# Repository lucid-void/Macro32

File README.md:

# Macro32

The Macro32 is a macropad featuring a stm32.
This project was a way for me to learn how to integrate an IC of my choosing on my PCB.
It was also my fist project using kicad

## Take a look

[kicad project](https://kicanvas.org/?github=https://github.com/KillrOfLife/Macro32/blob/main/PCB/macro32.kicad_pro)

## How can I make it myself

Great question!
Go look in the github releases for the latest tag
There you should find the downloads for the PCB production files (aka gerbers)
And the STL's for the case parts if you want that too. (you may need to download the source code)

## How to assemble

For any help assembling this macropad refer to the [build guide](https://github.com/KillrOfLife/Macro32/blob/main/buildguide.md).

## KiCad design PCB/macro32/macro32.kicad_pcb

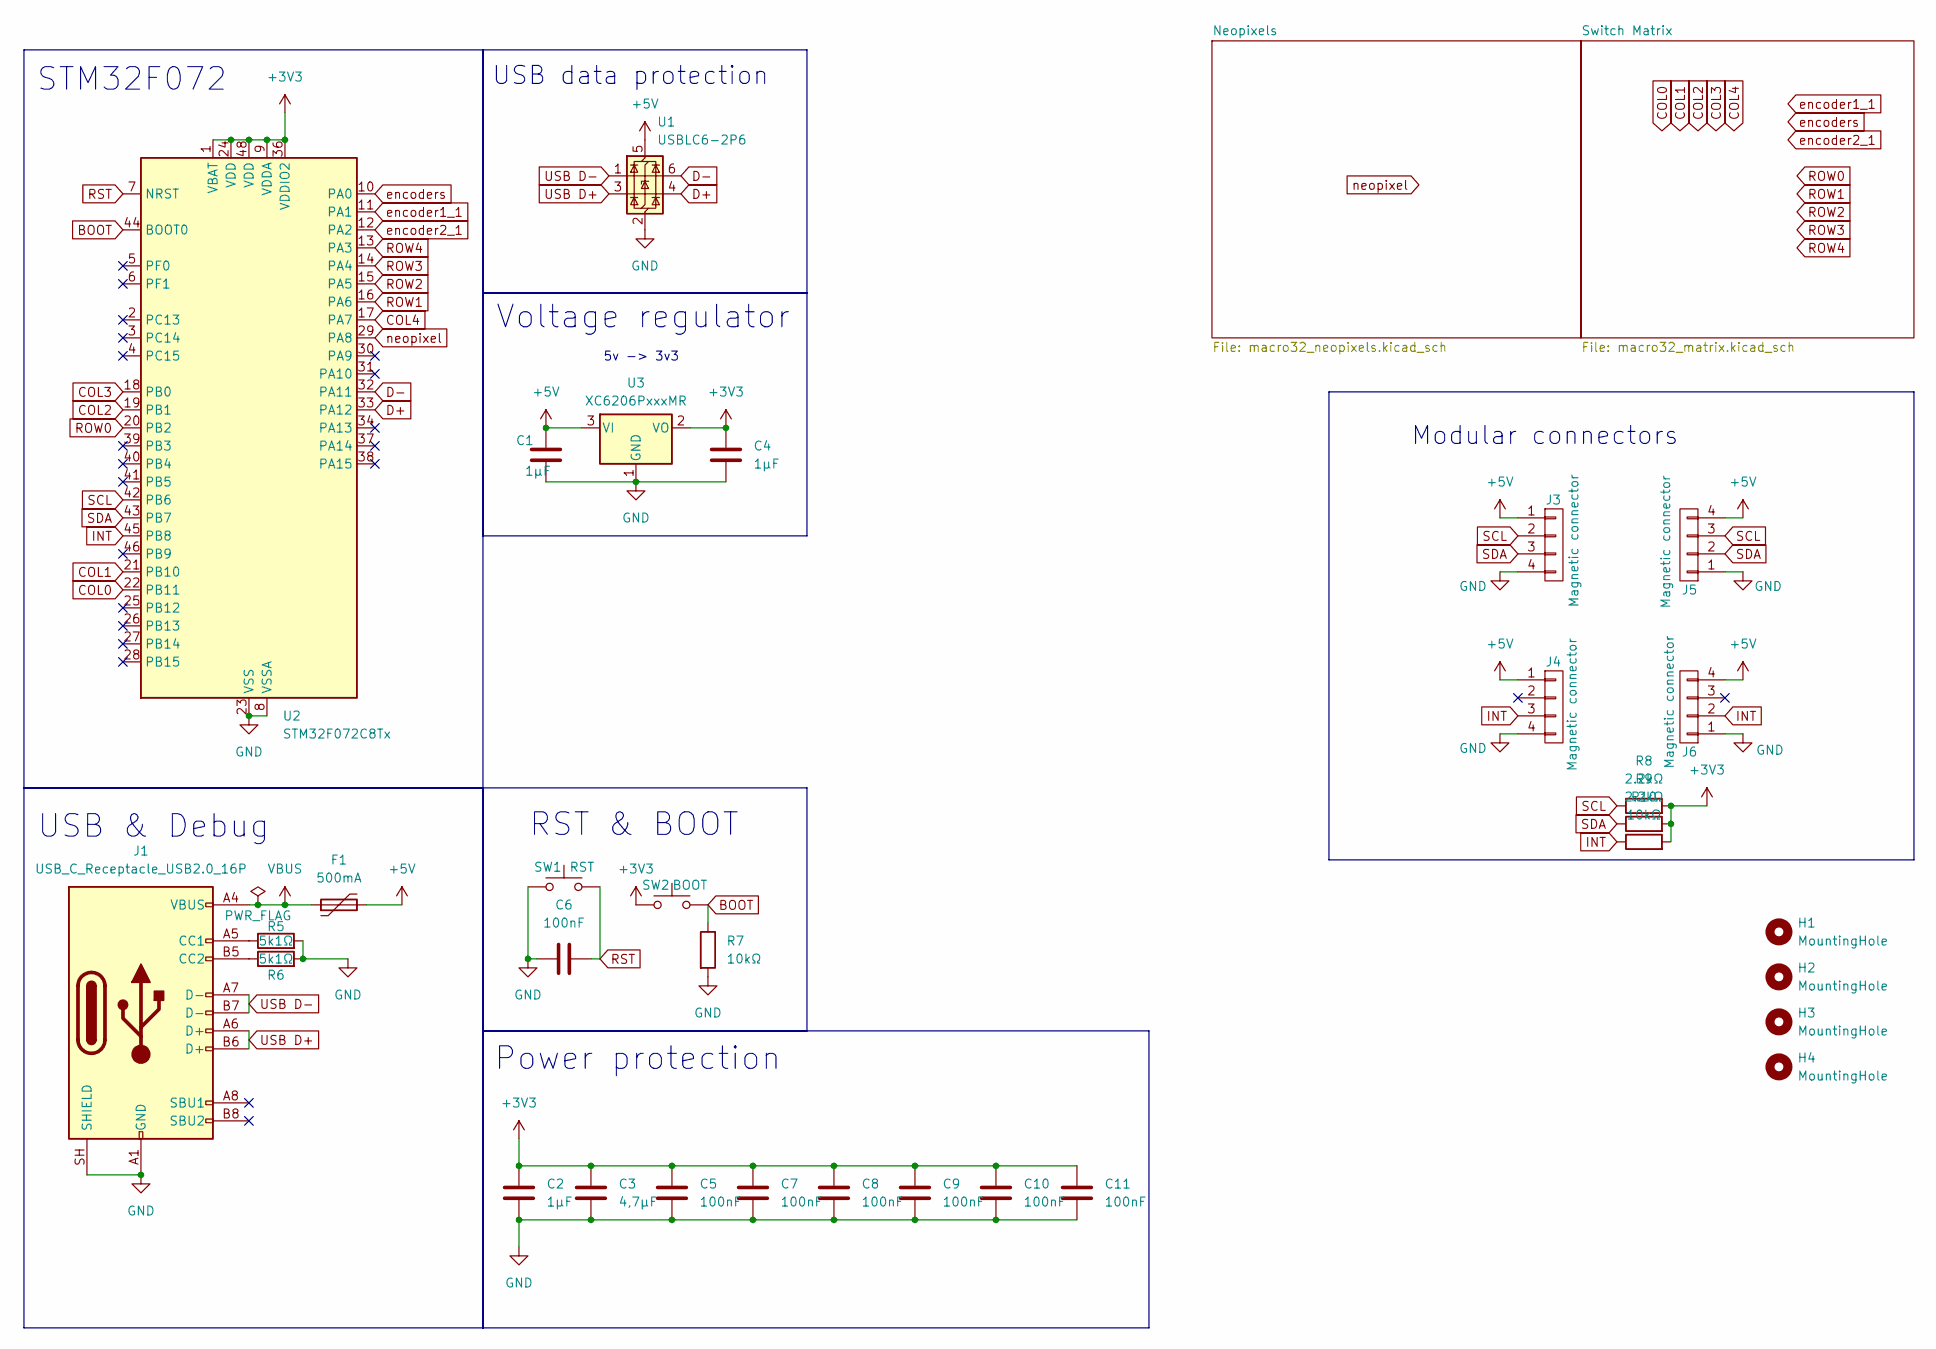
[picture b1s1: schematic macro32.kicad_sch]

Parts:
C1, C2, C4: 1μF; C_0805_2012Metric_Pad1.18x1.45mm_HandSolder
C3: 4,7μF; C_0805_2012Metric_Pad1.18x1.45mm_HandSolder
C5, C6, C7, C8, C9, C10, C11: 100nF; C_0805_2012Metric_Pad1.18x1.45mm_HandSolder
F1: 500mA; Resistor_1206
H1, H2, H3, H4: MountingHole; MountingHole_3.2mm_M3
J1: USB_C_Receptacle_USB2.0_16P; USB_C_Receptacle_GCT_USB4110
J3, J4, J5, J6: Magnetic connector; fakemag4pin90degFemale
R5, R6: 5k1Ω; Resistor_0805
R7, R10: 10kΩ; Resistor_0805
R8, R9: 2.2kΩ; Resistor_0805
SW1: RST; SW_SPST_TS-1088-xR020
SW2: BOOT; SW_SPST_TS-1088-xR020
U1: USBLC6-2P6; SOT-666
U2: STM32F072C8Tx; LQFP-48_7x7mm_P0.5mm
U3: XC6206PxxxMR; SOT-23-3

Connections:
+3V3: C2.1, C3.1, C4.1, C5.1, C7.1, C8.1, C9.1, C10.1, C11.1, R8.2, R9.2, R10.2, SW2.1, U2.1 (VBAT), U2.9 (VDDA), U2.24 (VDD), U2.36 (VDDIO2), U2.48 (VDD), U3.2 (VO)
+5V: C1.1, F1.2, J3.1, J4.1, J5.4, J6.4, U1.5 (VBUS), U3.3 (VI); also elsewhere on the board
BOOT: R7.1, SW2.2, U2.44 (BOOT0)
COL0: U2.22 (PB11); also elsewhere on the board
COL1: U2.21 (PB10); also elsewhere on the board
COL2: U2.19 (PB1); also elsewhere on the board
COL3: U2.18 (PB0); also elsewhere on the board
COL4: U2.17 (PA7); also elsewhere on the board
D+: U1.4 (I/O2), U2.33 (PA12)
D-: U1.6 (I/O1), U2.32 (PA11)
GND: C1.2, C2.2, C3.2, C4.2, C5.2, C6.1, C7.2, C8.2, C9.2, C10.2, C11.2, J1.A1 (GND), J1.A12 (GND), J1.B1 (GND), J1.B12 (GND), J1.SH (SHIELD), J3.4, J4.4, J5.1, J6.1, R5.2, R6.2, R7.2, SW1.1, U1.2 (GND), U2.8 (VSSA), U2.23 (VSS), U2.35 (VSS), U2.47 (VSS), U3.1 (GND); also elsewhere on the board
INT: J4.3, J6.2, R10.1, U2.45 (PB8)
unnamed: J1.A5 (CC1), R5.1
unnamed: J1.B5 (CC2), R6.1
ROW0: U2.20 (PB2); also elsewhere on the board
ROW1: U2.16 (PA6); also elsewhere on the board
ROW2: U2.15 (PA5); also elsewhere on the board
ROW3: U2.14 (PA4); also elsewhere on the board
ROW4: U2.13 (PA3); also elsewhere on the board
RST: C6.2, SW1.2, U2.7 (NRST)
SCL: J3.2, J5.3, R8.1, U2.42 (PB6)
SDA: J3.3, J5.2, R9.1, U2.43 (PB7)
USB D+: J1.A6 (D+), J1.B6 (D+), U1.3 (I/O2)
USB D-: J1.A7 (D-), J1.B7 (D-), U1.1 (I/O1)
VBUS: F1.1, J1.A4 (VBUS), J1.A9 (VBUS), J1.B4 (VBUS), J1.B9 (VBUS)
encoder1_1: U2.11 (PA1); also elsewhere on the board
encoder2_1: U2.12 (PA2); also elsewhere on the board
encoders: U2.10 (PA0); also elsewhere on the board
neopixel: U2.29 (PA8); also elsewhere on the board

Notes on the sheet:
STM32F072
RST & BOOT
USB data protection
Modular connectors
5v -> 3v3
USB & Debug
Voltage regulator
Power protection

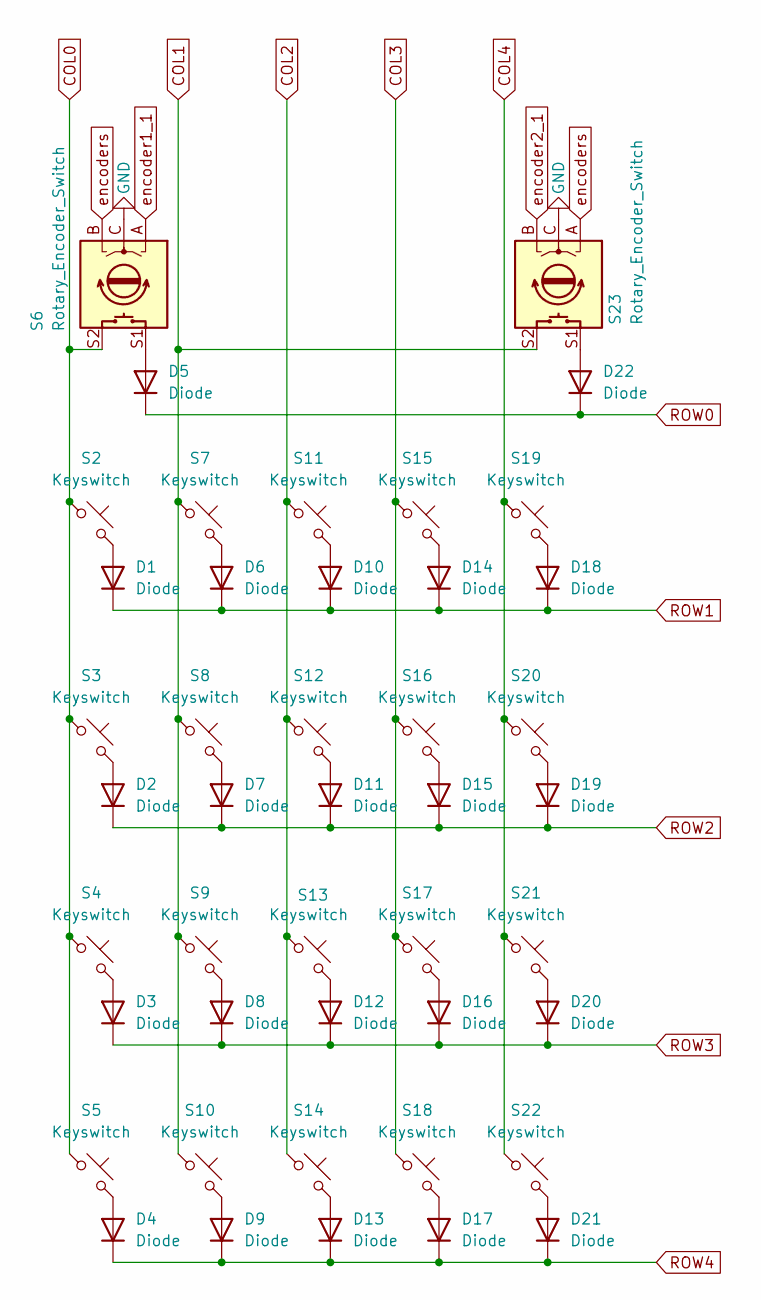
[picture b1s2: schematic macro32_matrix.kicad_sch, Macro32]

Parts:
D1, D2, D3, D4, D5, D6, D7, D8, D9, D10, D11, D12, D13, D14, D15, D16, D17, D18, D19, D20, D21, D22: Diode; Diode_combo
S2, S3, S4, S5, S7, S8, S9, S10, S11, S12, S13, S14, S15, S16, S17, S18, S19, S20, S21, S22: Keyswitch; Hotswap_MX_Plated_1.00u
S6, S23: Rotary_Encoder_Switch; keyswitch_cherrymx_hotswap_1u_rotary_encoder_ec12_1

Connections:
COL0: S2.1, S3.1, S4.1, S5.1, S6.S2; also elsewhere on the board
COL1: S7.1, S8.1, S9.1, S10.1, S23.S2; also elsewhere on the board
COL2: S11.1, S12.1, S13.1, S14.1; also elsewhere on the board
COL3: S15.1, S16.1, S17.1, S18.1; also elsewhere on the board
COL4: S19.1, S20.1, S21.1, S22.1; also elsewhere on the board
GND: S6.C, S23.C; also elsewhere on the board
unnamed: D1.2 (A), S2.2
unnamed: D2.2 (A), S3.2
unnamed: D3.2 (A), S4.2
unnamed: D4.2 (A), S5.2
unnamed: D5.2 (A), S6.S1
unnamed: D6.2 (A), S7.2
unnamed: D7.2 (A), S8.2
unnamed: D8.2 (A), S9.2
unnamed: D9.2 (A), S10.2
unnamed: D10.2 (A), S11.2
unnamed: D11.2 (A), S12.2
unnamed: D12.2 (A), S13.2
unnamed: D13.2 (A), S14.2
unnamed: D14.2 (A), S15.2
unnamed: D15.2 (A), S16.2
unnamed: D16.2 (A), S17.2
unnamed: D17.2 (A), S18.2
unnamed: D18.2 (A), S19.2
unnamed: D19.2 (A), S20.2
unnamed: D20.2 (A), S21.2
unnamed: D21.2 (A), S22.2
unnamed: D22.2 (A), S23.S1
ROW0: D5.1 (K), D22.1 (K); also elsewhere on the board
ROW1: D1.1 (K), D6.1 (K), D10.1 (K), D14.1 (K), D18.1 (K); also elsewhere on the board
ROW2: D2.1 (K), D7.1 (K), D11.1 (K), D15.1 (K), D19.1 (K); also elsewhere on the board
ROW3: D3.1 (K), D8.1 (K), D12.1 (K), D16.1 (K), D20.1 (K); also elsewhere on the board
ROW4: D4.1 (K), D9.1 (K), D13.1 (K), D17.1 (K), D21.1 (K); also elsewhere on the board
encoder1_1: S6.A; also elsewhere on the board
encoder2_1: S23.B; also elsewhere on the board
encoders: S6.B, S23.A; also elsewhere on the board

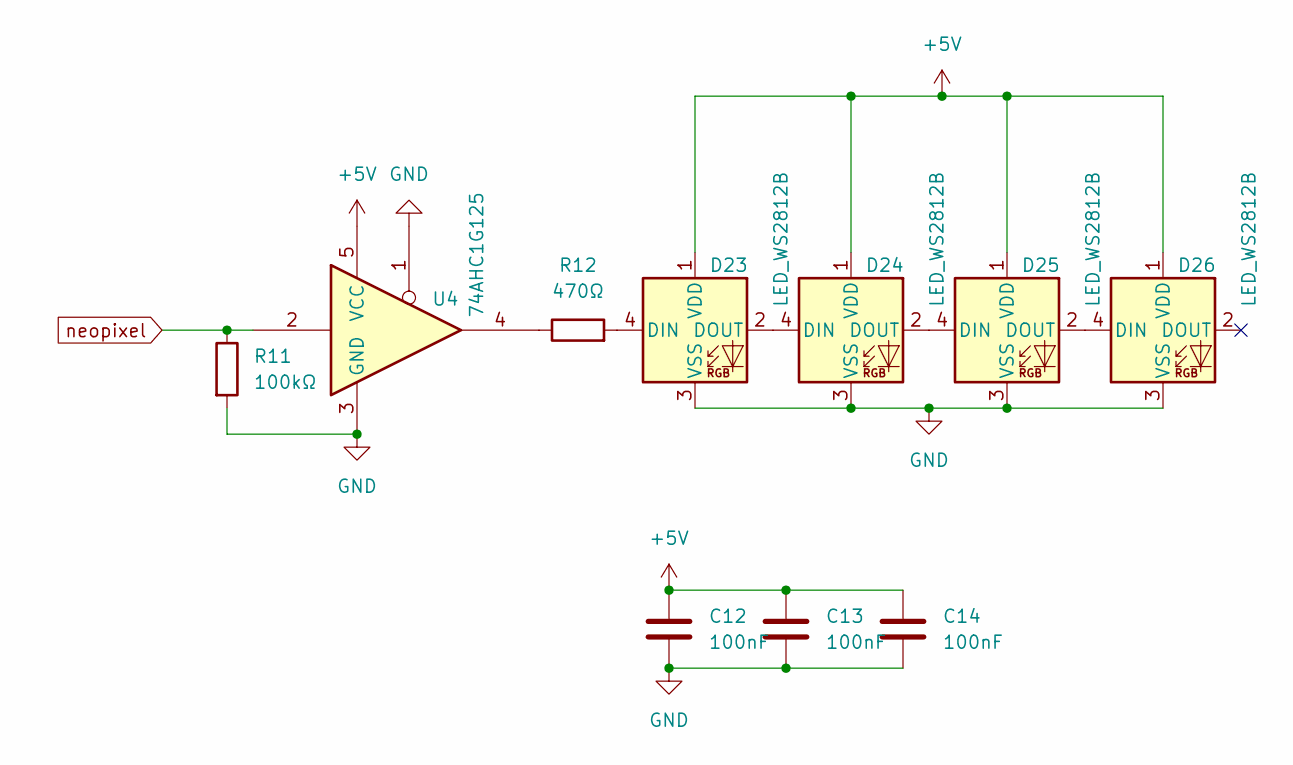
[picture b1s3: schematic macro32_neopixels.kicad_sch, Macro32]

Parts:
C12, C13, C14: 100nF; C_0805_2012Metric_Pad1.18x1.45mm_HandSolder
D23, D24, D25, D26: LED_WS2812B
R11: 100kΩ; Resistor_0805
R12: 470Ω; Resistor_0805
U4: 74AHC1G125; SOT-353_SC-70-5

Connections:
+5V: C12.1, C13.1, C14.1, D23.1 (VDD), D24.1 (VDD), D25.1 (VDD), D26.1 (VDD), U4.5 (VCC); also elsewhere on the board
GND: C12.2, C13.2, C14.2, D23.3 (VSS), D24.3 (VSS), D25.3 (VSS), D26.3 (VSS), R11.2, U4.1, U4.3 (GND); also elsewhere on the board
unnamed: D23.4 (DIN), R12.2
unnamed: D23.2 (DOUT), D24.4 (DIN)
unnamed: D24.2 (DOUT), D25.4 (DIN)
unnamed: D25.2 (DOUT), D26.4 (DIN)
unnamed: R12.1, U4.4
neopixel: R11.1, U4.2; also elsewhere on the board

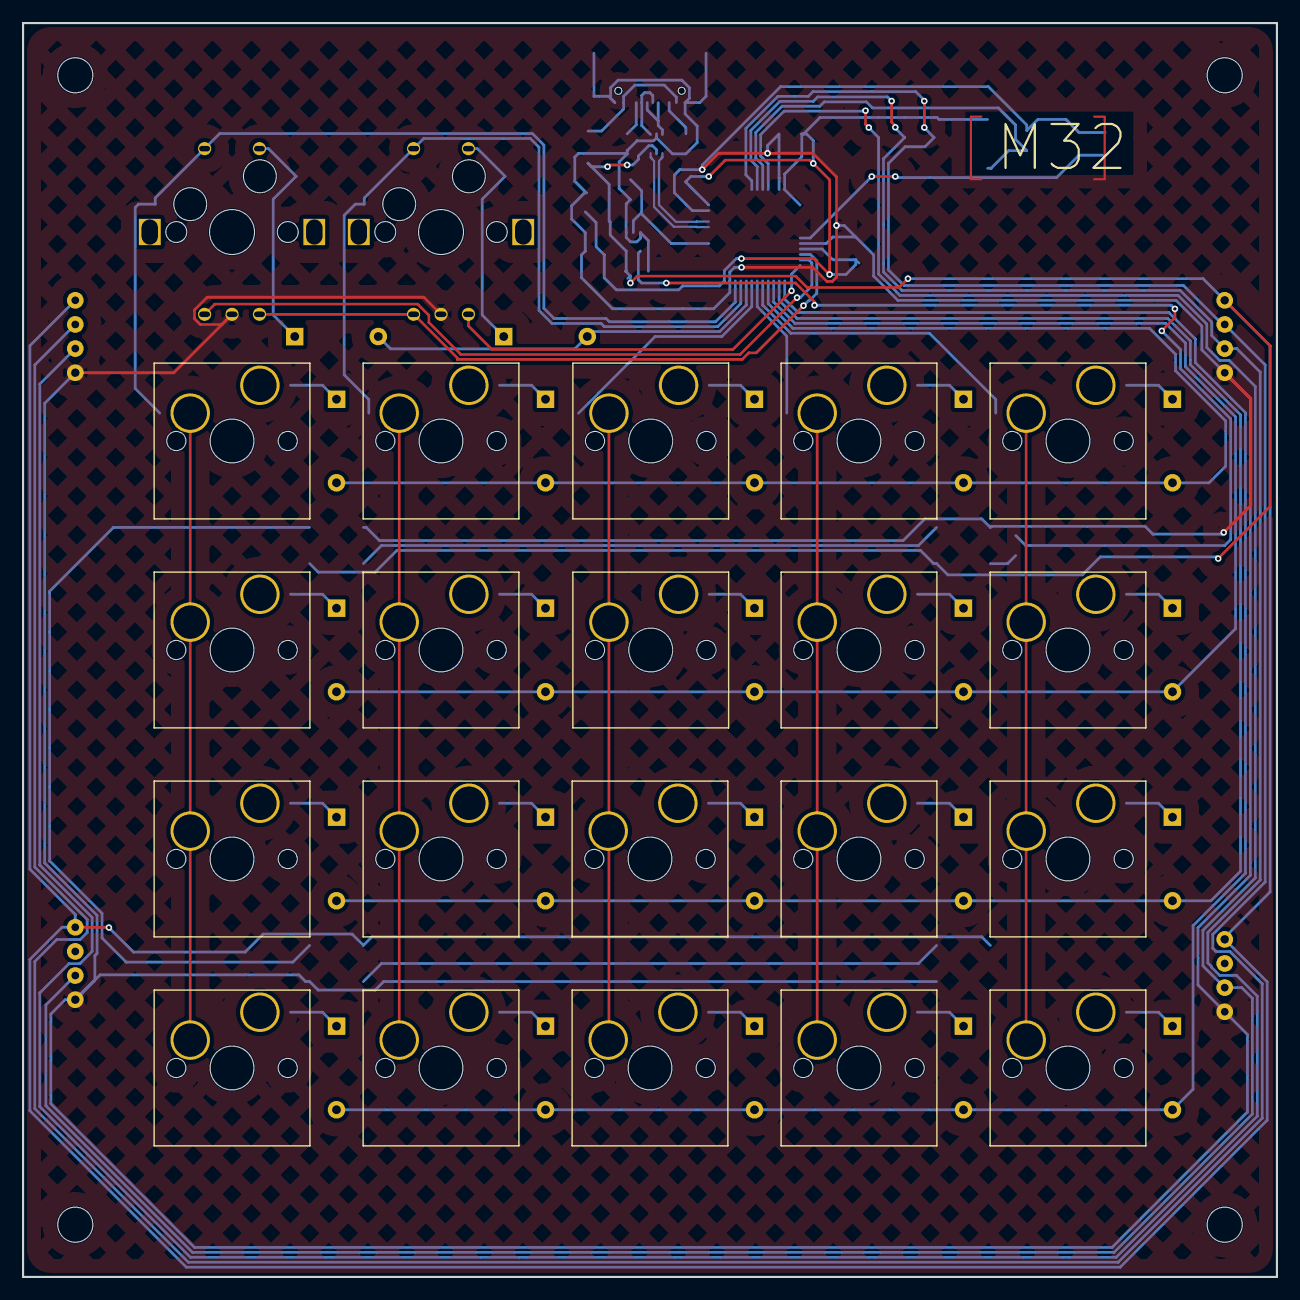
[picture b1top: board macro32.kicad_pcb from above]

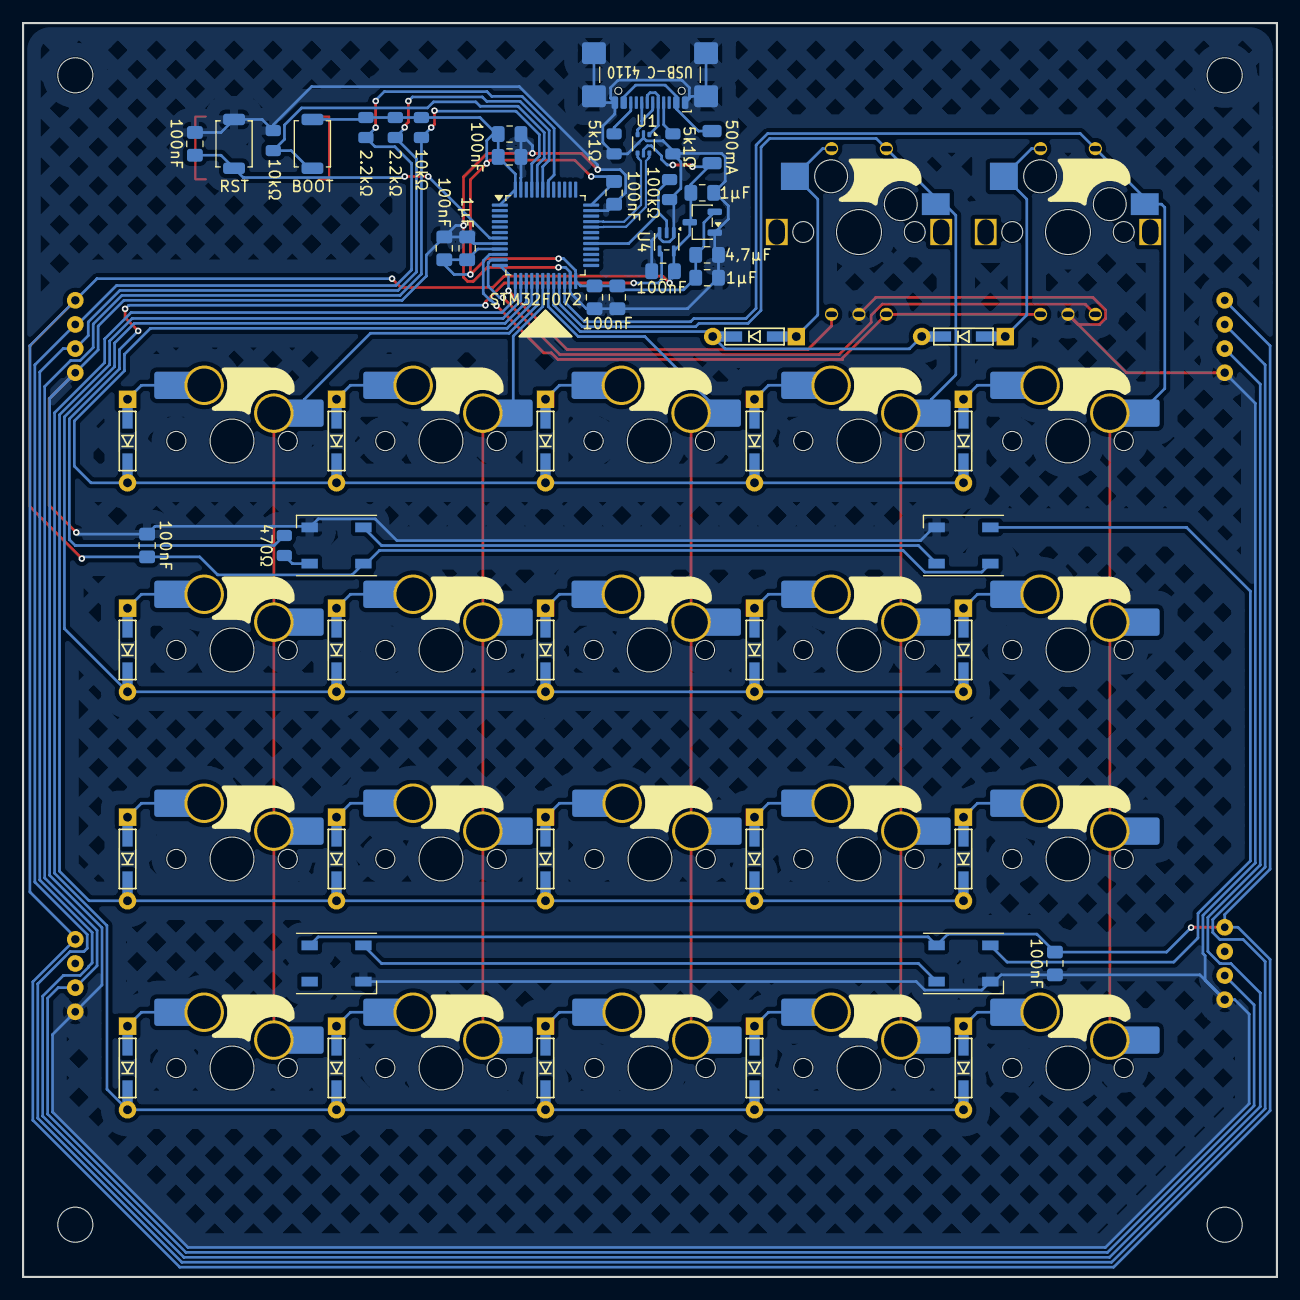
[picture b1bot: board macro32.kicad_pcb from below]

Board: 2 copper layers, 114.3 x 114.3 mm, 86 parts (62 on the bottom side), 56 nets.

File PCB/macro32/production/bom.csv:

Designator,Footprint,Quantity,Value,LCSC Part #
"C1, C2, C4",0805,3,1μF,
"C10, C11, C12, C13, C14, C5, C6, C7, C8, C9",0805,10,100nF,
C3,0805,1,"4,7μF",
"D1, D10, D11, D12, D13, D14, D15, D16, D17, D18, D19, D2, D20, D21, D22, D3, D4, D5, D6, D7, D8, D9",Diode_combo,22,Diode,
"D23, D24, D25, D26",LED_WS2812B,4,LED_WS2812B,
F1,Resistor_1206,1,500mA,
J1,USB_C_Receptacle_GCT_USB4110,1,USB_C_Receptacle_USB2.0_16P,
"J3, J4, J5, J6",fakemag4pin90degFemale,4,Magnetic connector,
"R10, R7",Resistor_0805,2,10kΩ,
R11,Resistor_0805,1,100kΩ,
R12,Resistor_0805,1,470Ω,
"R5, R6",Resistor_0805,2,5k1Ω,
"R8, R9",Resistor_0805,2,2.2kΩ,
"S10, S11, S12, S13, S14, S15, S16, S17, S18, S19, S2, S20, S21, S22, S3, S4, S5, S7, S8, S9",Hotswap_MX_Plated_1.00u,20,Keyswitch,
"S23, S6",keyswitch_cherrymx_hotswap_1u_rotary_encoder_ec12_1,2,Rotary_Encoder_Switch,
SW1,SW_SPST_TS-1088-xR020,1,RST,
SW2,SW_SPST_TS-1088-xR020,1,BOOT,
U1,SOT-666,1,USBLC6-2P6,
U2,LQFP-48_7x7mm_P0.5mm,1,STM32F072,
U3,SOT-23-3,1,XC6206PxxxMR,
U4,SOT-353_SC-70-5,1,74AHC1G125,

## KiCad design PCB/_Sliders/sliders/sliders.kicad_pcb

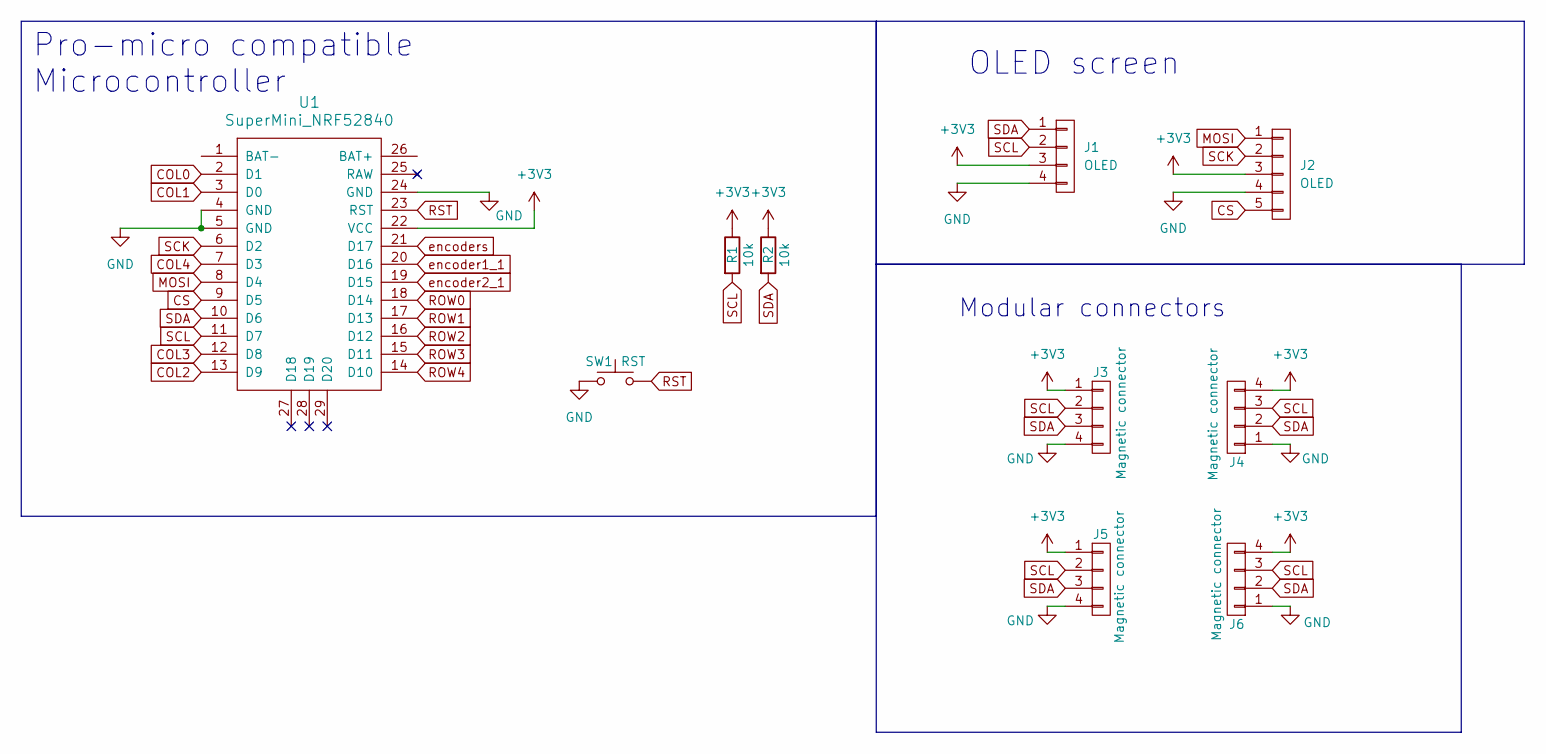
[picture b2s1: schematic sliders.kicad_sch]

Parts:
J1: OLED; OLED_4Pin
J2: OLED; OLED_5Pin
J3, J5: Magnetic connector; fakemag4pin90degFemale
J4, J6: Magnetic connector; fakemag4pin90degMale
R1, R2: 10k; R_0805_2012Metric_Pad1.20x1.40mm_HandSolder
SW1: RST; SW_SPST_TS-1088-xR020
U1: SuperMini_NRF52840; SuperMini_NRF52850_pro_micro

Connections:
+3V3: J1.3, J2.3, J3.1, J4.4, J5.1, J6.4, R1.1, R2.1, U1.22 (VCC)
COL0: U1.2 (D1)
COL1: U1.3 (D0)
COL2: U1.13 (D9)
COL3: U1.12 (D8)
COL4: U1.7 (D3)
CS: J2.5 (P4), U1.9 (D5)
GND: J1.4, J2.4, J3.4, J4.1, J5.4, J6.1, SW1.1, U1.4 (GND), U1.5 (GND), U1.24 (GND)
MOSI: J2.1, U1.8 (D4)
ROW0: U1.18 (D14)
ROW1: U1.17 (D13)
ROW2: U1.16 (D12)
ROW3: U1.15 (D11)
ROW4: U1.14 (D10)
RST: SW1.2, U1.23 (RST)
SCK: J2.2, U1.6 (D2)
SCL: J1.2, J3.2, J4.3, J5.2, J6.3, R1.2, U1.11 (D7)
SDA: J1.1, J3.3, J4.2, J5.3, J6.2, R2.2, U1.10 (D6)
encoder1_1: U1.20 (D16)
encoder2_1: U1.19 (D15)
encoders: U1.21 (D17)

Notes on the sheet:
OLED screen
Modular connectors
Pro-micro compatible Microcontroller

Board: 2 copper layers, 10 parts (0 on the bottom side), 8 nets, no tracks yet.

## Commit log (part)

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2025-11-20 cleanup
2025-11-20 Schematic and PCB v2.0 moved files to seperate folder
2025-11-20 gitignore
2025-11-20 keyboard layout json
2025-12-13 PCB V2 design
